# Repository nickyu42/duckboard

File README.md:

# Duckboard

This repository contains the PCB design for a 4x4 macroboard with a rotary encoder.  

</img>

## Fusion360 Model and Case

</img>

</img>

## Schematic

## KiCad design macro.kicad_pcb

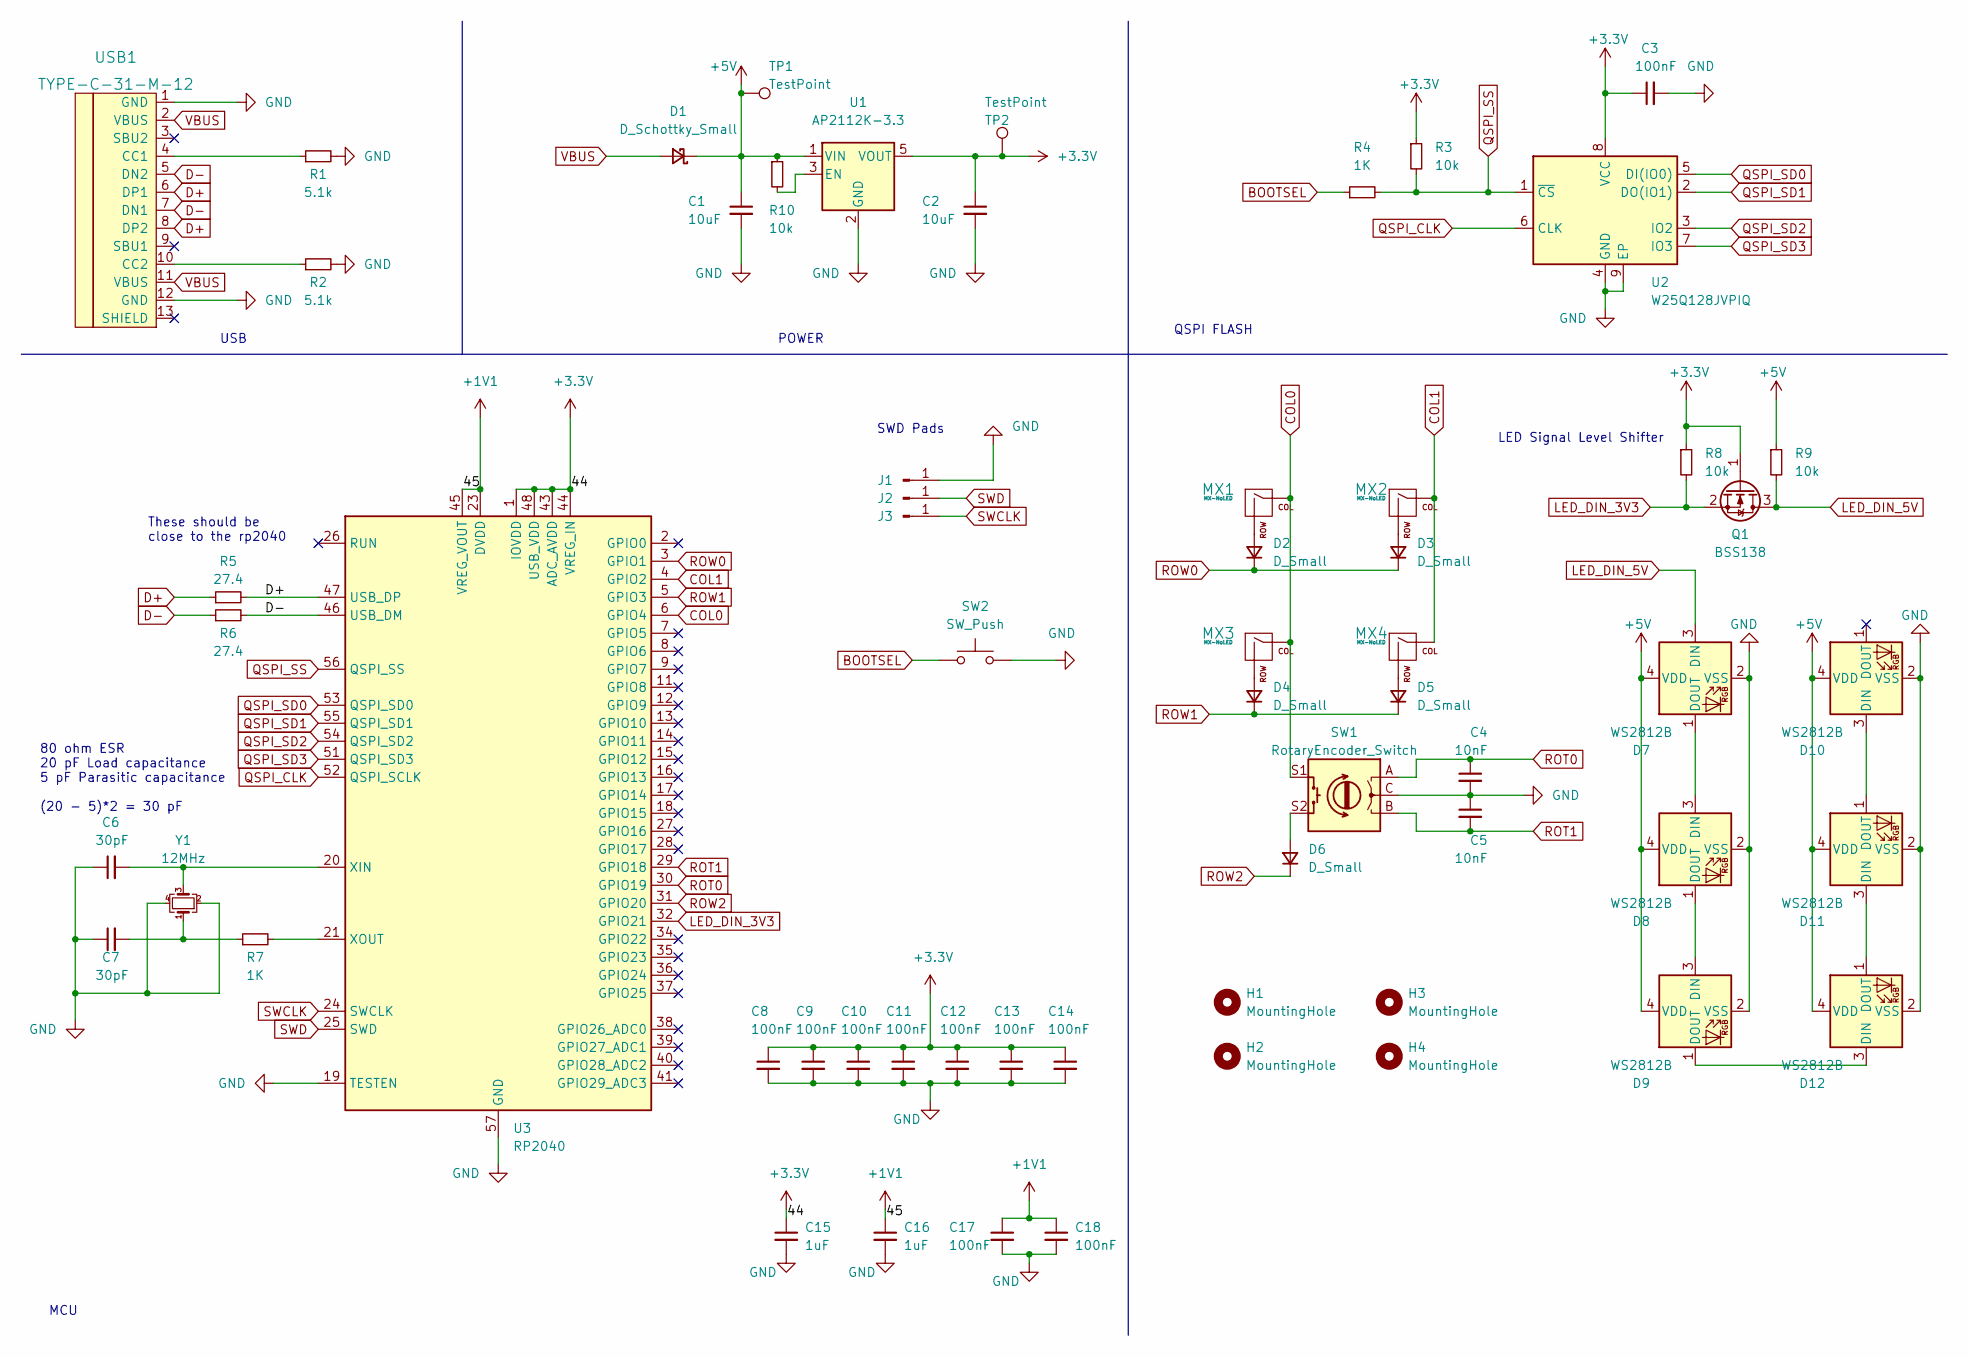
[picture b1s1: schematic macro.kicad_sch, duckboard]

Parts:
C1, C2: 10uF; C_0402_1005Metric
C3, C8, C9, C10, C11, C12, C13, C14, C17, C18: 100nF; C_0402_1005Metric
C4, C5: 10nF; C_0402_1005Metric
C6, C7: 30pF; C_0402_1005Metric
C15, C16: 1uF; C_0402_1005Metric
D1: D_Schottky_Small; D_SOD-323
D2, D3, D4, D5, D6: D_Small; D_SOD-323
D7, D8, D9, D10, D11, D12: WS2812B; LED_WS2812B-2020_PLCC4_2.0x2.0mm
H1, H2, H3, H4: MountingHole; MountingHole_2.2mm_M2
J1, J2, J3: Conn_01x01_Male; TestPoint_Pad_2.0x2.0mm
MX1, MX2, MX3, MX4: MX-NoLED; MX-1U-NoLED
Q1: BSS138; SOT-23
R1, R2: 5.1k; R_0402_1005Metric
R3, R8, R9, R10: 10k; R_0402_1005Metric
R4, R7: 1K; R_0402_1005Metric
R5, R6: 27.4; R_0402_1005Metric
SW1: RotaryEncoder_Switch; RotaryEncoder_Alps_EC11E-Switch_Vertical_H20mm_CircularMoun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
SW2: SW_Push; SW_KMR221GLFS
TP1, TP2: TestPoint; TestPoint_Pad_D1.0mm
U1: AP2112K-3.3; SOT-23-5
U2: W25Q128JVPIQ; WSON-8-1EP_6x5mm_P1.27mm_EP3.4x4.3mm
U3: RP2040; QFN-56-1EP_7x7mm_P0.4mm_EP3.2x3.2mm
USB1: TYPE-C-31-M-12; HRO_TYPE-C-31-M-12
Y1: 12MHz; Crystal_SMD_3225-4Pin_3.2x2.5mm

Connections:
+1V1: C16.1, C17.1, C18.1, U3.23 (DVDD), U3.45 (VREG_VOUT), U3.50 (DVDD)
+3.3V: C2.1, C3.1, C8.1, C9.1, C10.1, C11.1, C12.1, C13.1, C14.1, C15.1, Q1.1 (G), R3.1, R8.1, TP2.1, U1.5 (VOUT), U2.8 (VCC), U3.1 (IOVDD), U3.10 (IOVDD), U3.22 (IOVDD), U3.33 (IOVDD), U3.42 (IOVDD), U3.43 (ADC_AVDD), U3.44 (VREG_IN), U3.48 (USB_VDD), U3.49 (IOVDD)
+5V: C1.1, D1.1 (K), D7.4 (VDD), D8.4 (VDD), D9.4 (VDD), D10.4 (VDD), D11.4 (VDD), D12.4 (VDD), R9.1, R10.1, TP1.1, U1.1 (VIN)
BOOTSEL: R4.1, SW2.1
COL0: MX1.1 (COL), MX3.1 (COL), SW1.S1, U3.6 (GPIO4)
COL1: MX2.1 (COL), MX4.1 (COL), U3.4 (GPIO2)
D+: R5.1, R5.2, U3.47 (USB_DP), USB1.6 (DP1), USB1.8 (DP2)
D-: R6.1, R6.2, U3.46 (USB_DM), USB1.5 (DN2), USB1.7 (DN1)
GND: C1.2, C2.2, C3.2, C4.2, C5.1, C6.1, C7.1, C8.2, C9.2, C10.2, C11.2, C12.2, C13.2, C14.2, C15.2, C16.2, C17.2, C18.2, D7.2 (VSS), D8.2 (VSS), D9.2 (VSS), D10.2 (VSS), D11.2 (VSS), D12.2 (VSS), J1.1, R1.2, R2.2, SW1.C, SW2.2, SW2.5, U1.2 (GND), U2.4 (GND), U2.9 (EP), U3.19 (TESTEN), U3.57 (GND), USB1.1 (GND), USB1.12 (GND), Y1.2, Y1.4
LED_DIN_3V3: Q1.2 (S), R8.2, U3.32 (GPIO21)
LED_DIN_5V: D7.3 (DIN), Q1.3 (D), R9.2
unnamed: C6.2, U3.20 (XIN), Y1.3
unnamed: C7.2, R7.1, Y1.1
unnamed: D2.2 (A), MX1.2 (ROW)
unnamed: D3.2 (A), MX2.2 (ROW)
unnamed: D4.2 (A), MX3.2 (ROW)
unnamed: D5.2 (A), MX4.2 (ROW)
unnamed: D6.2 (A), SW1.S2
unnamed: D7.1 (DOUT), D8.3 (DIN)
unnamed: D8.1 (DOUT), D9.3 (DIN)
unnamed: D10.3 (DIN), D11.1 (DOUT)
unnamed: D11.3 (DIN), D12.1 (DOUT)
unnamed: D9.1 (DOUT), D12.3 (DIN)
unnamed: R1.1, USB1.4 (CC1)
unnamed: R2.1, USB1.10 (CC2)
unnamed: R7.2, U3.21 (XOUT)
unnamed: R10.2, U1.3 (EN)
QSPI_CLK: U2.6 (CLK), U3.52 (QSPI_SCLK)
QSPI_SD0: U2.5 (DI(IO0)), U3.53 (QSPI_SD0)
QSPI_SD1: U2.2 (DO(IO1)), U3.55 (QSPI_SD1)
QSPI_SD2: U2.3 (IO2), U3.54 (QSPI_SD2)
QSPI_SD3: U2.7 (IO3), U3.51 (QSPI_SD3)
QSPI_SS: R3.2, R4.2, U2.1 (~CS), U3.56 (QSPI_SS)
ROT0: C4.1, SW1.A, U3.30 (GPIO19)
ROT1: C5.2, SW1.B, U3.29 (GPIO18)
ROW0: D2.1 (K), D3.1 (K), U3.3 (GPIO1)
ROW1: D4.1 (K), D5.1 (K), U3.5 (GPIO3)
ROW2: D6.1 (K), U3.31 (GPIO20)
SWCLK: J3.1, U3.24 (SWCLK)
SWD: J2.1, U3.25 (SWD)
VBUS: D1.2 (A), USB1.2 (VBUS), USB1.11 (VBUS)

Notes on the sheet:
These should be close to the rp2040
LED Signal Level Shifter
SWD Pads
80 ohm ESR 20 pF Load capacitance 5 pF Parasitic capacitance (20 - 5)*2 = 30 pF
POWER
QSPI FLASH
USB
MCU

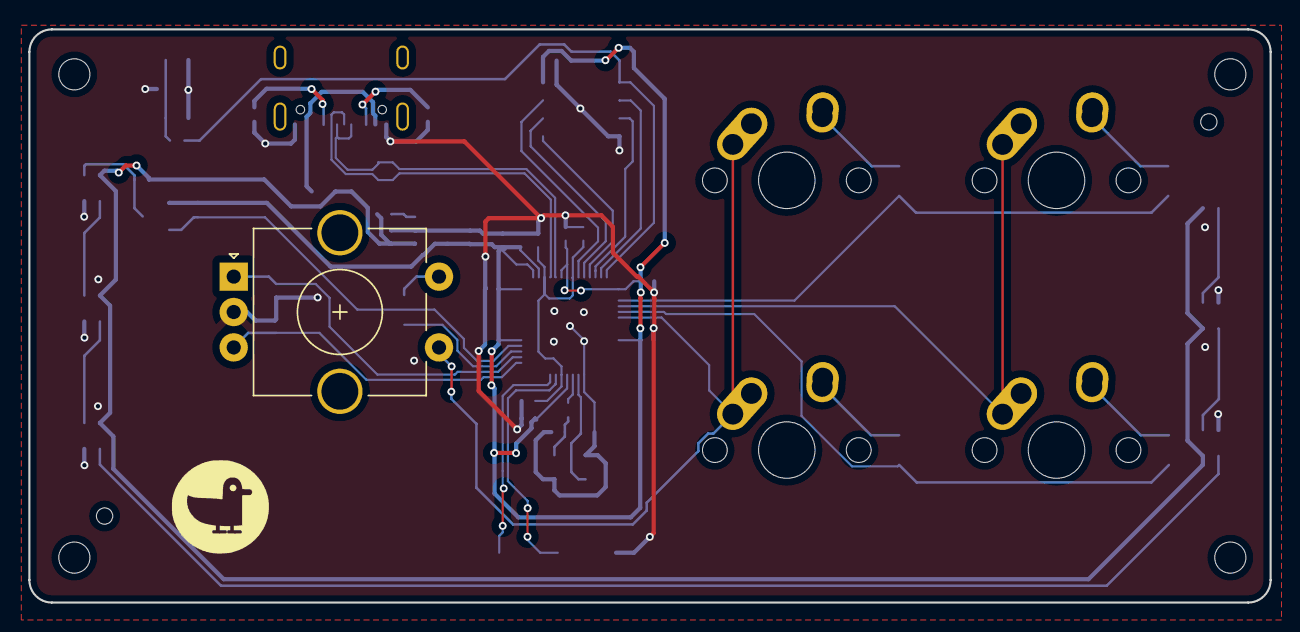
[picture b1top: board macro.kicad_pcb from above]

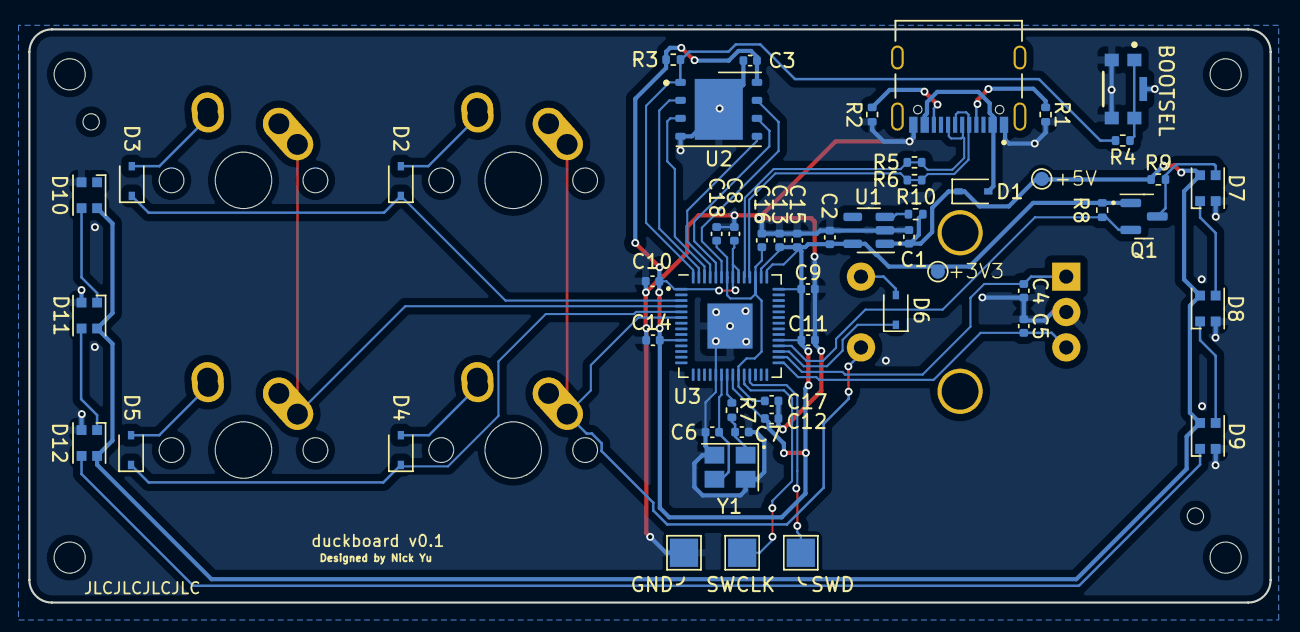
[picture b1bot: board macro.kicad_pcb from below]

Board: 2 copper layers, 87.7 x 40.5 mm, 61 parts (52 on the bottom side), 41 nets.

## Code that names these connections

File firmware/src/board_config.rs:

use rp2040_hal as hal;

#[link_section = ".boot2"]
#[no_mangle]
#[used]
static BOOT2_FIRMWARE: [u8; 256] = rp2040_boot2::BOOT_LOADER_W25Q080;

hal::bsp_pins!(
    Gpio1 { name: row0 },
    Gpio2 { name: col1 },
    Gpio3 { name: row1 },
    Gpio4 { name: col0 },
    Gpio18 { name: rot1 },
    Gpio19 { name: rot0 },
    Gpio20 { name: row2 },
    Gpio21 { name: led_out },
);

pub const XOSC_CRYSTAL_FREQ: u32 = 12_000_000;

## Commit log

2022-10-24 initial
2022-10-25 Add ws2812
2022-12-27 New design
2022-12-27 Rough placement
2022-12-29 LEDs
2022-12-29 Cleanup schematic
2022-12-29 Remove unused logo
2022-12-29 Add LED decoupling caps
2023-01-07 Add tooling holes and logo
2023-01-07 V0.1 Version
2023-01-11 Drill hole center
2023-01-11 Add .gitignore
2023-01-31 Add 3D models used
2023-01-31 Move to pcb folder
2023-01-31 Move footprints
2023-01-31 Add Fusion360 model
2023-03-01 Basic HID implementation
2023-03-01 Refactor
2023-03-02 Add RTIC
2023-03-02 Basic working peripherals in RTIC
2023-03-02 Bump cortex-m-rt
2023-03-11 Working HID
2023-03-11 Add keyboard mapping
2023-03-13 Fix HID issues
2023-03-13 Add cichlid and basic LED pattern
2023-04-04 Add ScanResult
